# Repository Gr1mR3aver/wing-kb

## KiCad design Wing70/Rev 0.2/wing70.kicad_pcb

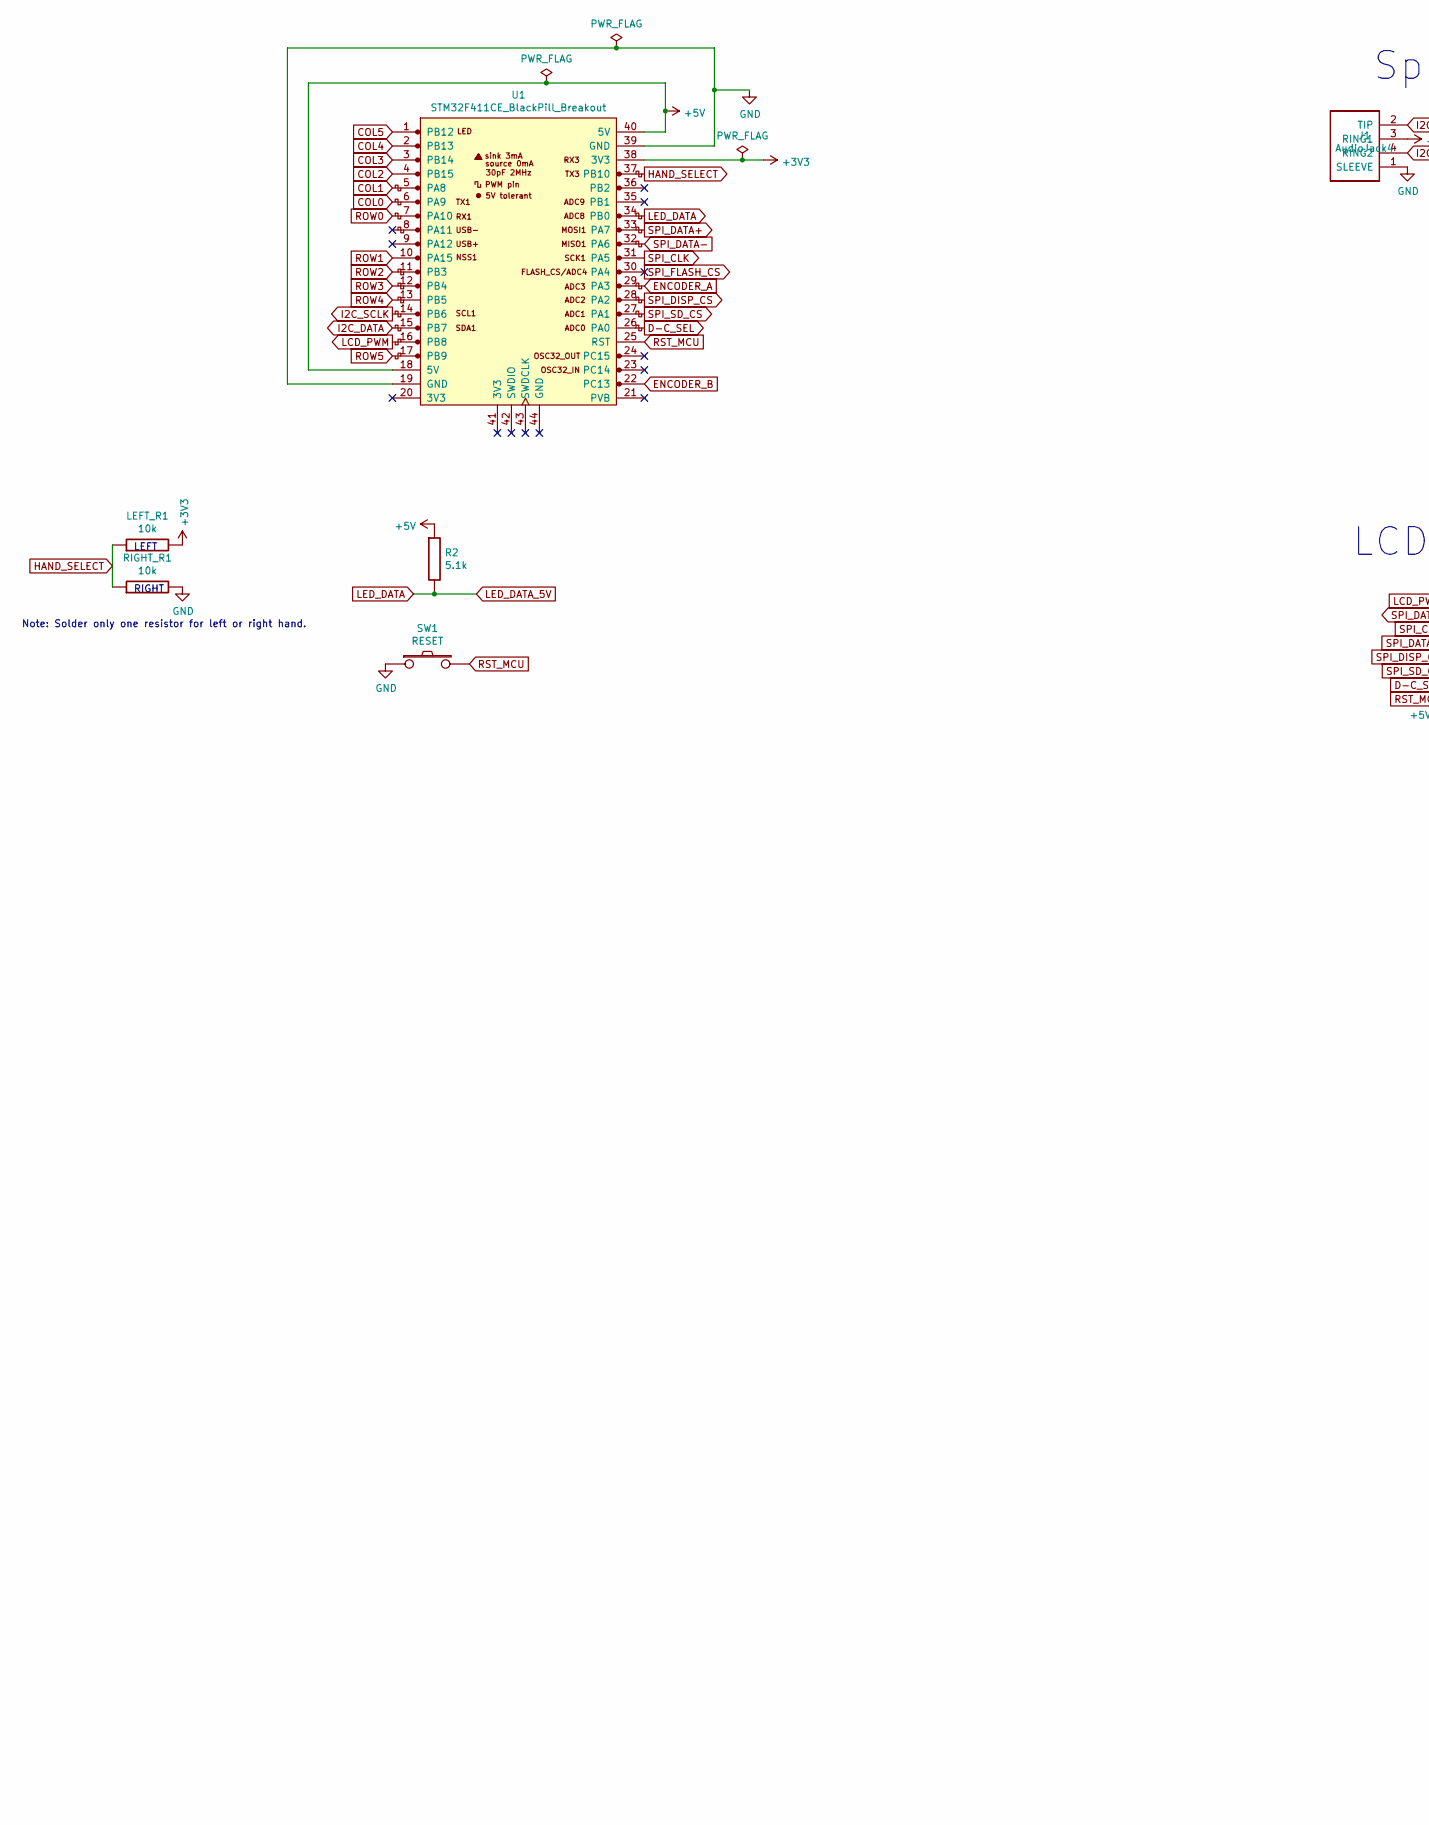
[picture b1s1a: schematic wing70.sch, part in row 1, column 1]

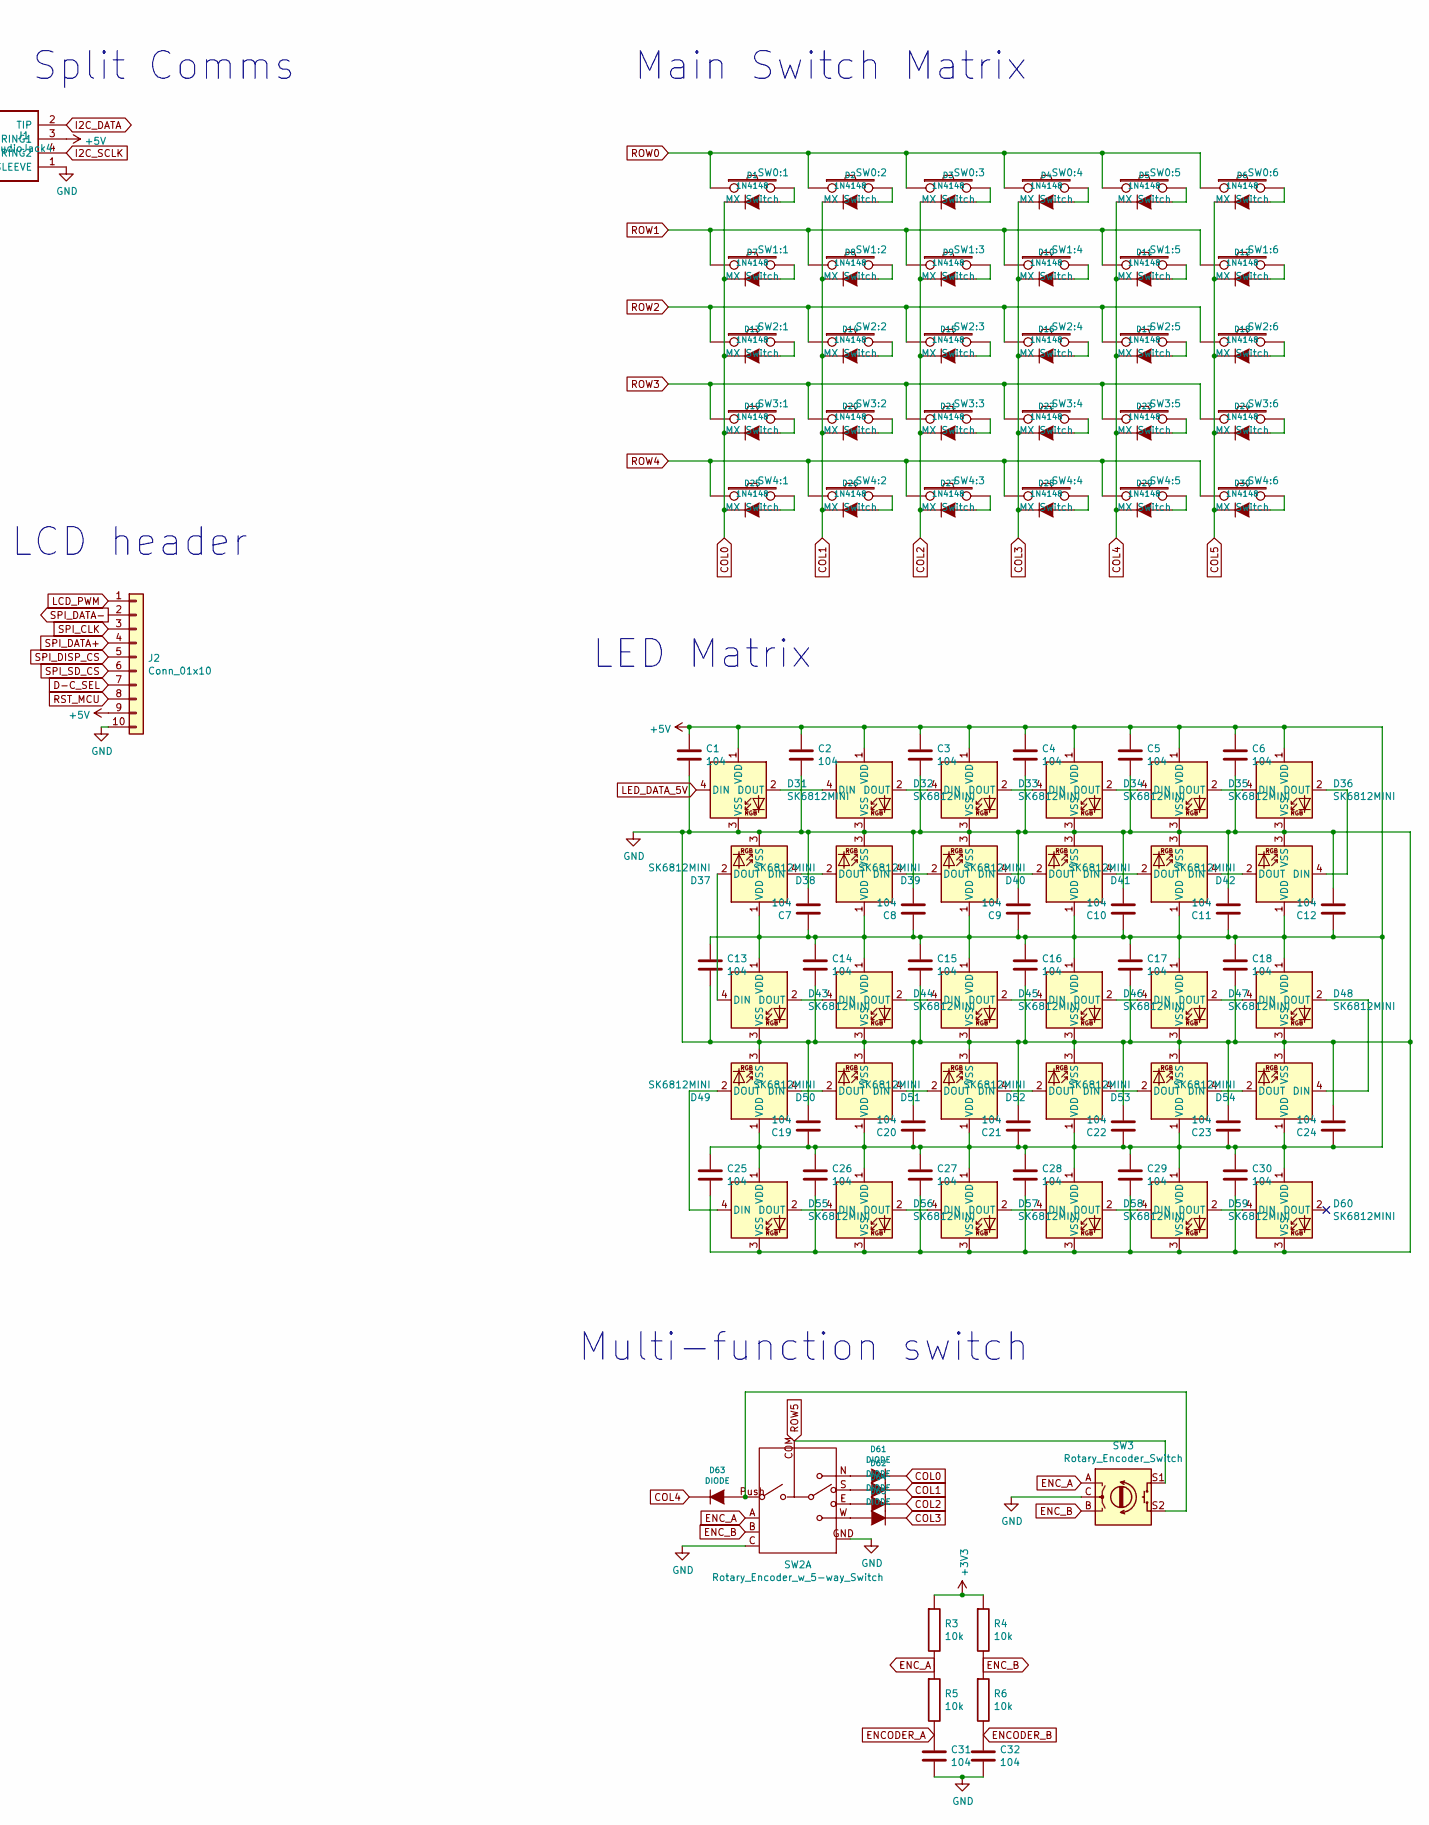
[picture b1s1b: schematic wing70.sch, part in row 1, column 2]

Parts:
C1, C2, C3, C4, C5, C6, C7, C8, C9, C10, C11, C12, C13, C14, C15, C16, C17, C18, C19, C20, C21, C22, C23, C24, C25, C26, C27, C28, C29, C30, C31, C32: 104; C_0805_2012Metric_Pad1.18x1.45mm_HandSolder
D1, D2, D3, D4, D5, D6, D7, D8, D9, D10, D11, D12, D13, D14, D15, D16, D17, D18, D19, D20, D21, D22, D23, D24, D25, D26, D27, D28, D29, D30: 1N4148; Add-on_diode_for_MX_socket
D31, D32, D33, D34, D35, D36, D37, D38, D39, D40, D41, D42, D43, D44, D45, D46, D47, D48, D49, D50, D51, D52, D53, D54, D55, D56, D57, D58, D59, D60: SK6812MINI; SK6812-MINI-E_reversible
D61, D62, D63, D64, D65: DIODE; Diode
J1: AudioJack4; TRRS_Jack_reversible_with_pads
J2: Conn_01x10; 1.8in_TFT_reversible-169x128_color-breakout
LEFT_R1: 10k; R_0805_2012Metric_Pad1.20x1.40mm_HandSolder
R2: 5.1k; R_0805_2012Metric_Pad1.20x1.40mm_HandSolder
R3, R4, R5, R6: 10k; R_0805_2012Metric_Pad1.20x1.40mm_HandSolder
RIGHT_R1: 10k; R_0805_2012Metric_Pad1.20x1.40mm_HandSolder
SW0:1, SW0:2, SW0:3, SW0:4, SW0:5, SW0:6, SW1:1, SW1:2, SW1:3, SW1:4, SW1:5, SW1:6, SW2:1, SW2:2, SW2:3, SW2:4, SW2:5, SW2:6, SW3:1, SW3:2, SW3:3, SW3:4, SW3:5, SW3:6, SW4:1, SW4:2, SW4:3, SW4:4, SW4:5, SW4:6: MX Switch; Kailh_socket_MX_optional_reversible
SW1: RESET; SW_Tactile_SPST_Angled_MJTP1117
SW2: Rotary_Encoder_w_5-way_Switch; RKJXT1F_reversible_EW_solder_jumpers
SW3: Rotary_Encoder_Switch; RotaryEncoder_Alps_EC11E-Switch_Vertical_H20mm
U1: STM32F411CE_BlackPill_Breakout; Blackpill_STM32F411CE

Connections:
+3V3: LEFT_R1.2, R3.1, R4.1, U1.38 (3V3)
+5V: C1.1, C2.1, C3.1, C4.1, C5.1, C6.1, C7.1, C8.1, C9.1, C10.1, C11.1, C12.1, C13.1, C14.1, C15.1, C16.1, C17.1, C18.1, C19.1, C20.1, C21.1, C22.1, C23.1, C24.1, C25.1, C26.1, C27.1, C28.1, C29.1, C30.1, D31.1 (VDD), D32.1 (VDD), D33.1 (VDD), D34.1 (VDD), D35.1 (VDD), D36.1 (VDD), D37.1 (VDD), D38.1 (VDD), D39.1 (VDD), D40.1 (VDD), D41.1 (VDD), D42.1 (VDD), D43.1 (VDD), D44.1 (VDD), D45.1 (VDD), D46.1 (VDD), D47.1 (VDD), D48.1 (VDD), D49.1 (VDD), D50.1 (VDD), D51.1 (VDD), D52.1 (VDD), D53.1 (VDD), D54.1 (VDD), D55.1 (VDD), D56.1 (VDD), D57.1 (VDD), D58.1 (VDD), D59.1 (VDD), D60.1 (VDD), J1.3 (RING1), J2.9, R2.1, U1.18 (5V), U1.40 (5V)
COL0: D1.2 (K), D7.2 (K), D13.2 (K), D19.2 (K), D25.2 (K), D61.2 (K), U1.6 (PA9)
COL1: D2.2 (K), D8.2 (K), D14.2 (K), D20.2 (K), D26.2 (K), D62.2 (K), U1.5 (PA8)
COL2: D3.2 (K), D9.2 (K), D15.2 (K), D21.2 (K), D27.2 (K), D64.2 (K), U1.4 (PB15)
COL3: D4.2 (K), D10.2 (K), D16.2 (K), D22.2 (K), D28.2 (K), D65.2 (K), U1.3 (PB14)
COL4: D5.2 (K), D11.2 (K), D17.2 (K), D23.2 (K), D29.2 (K), D63.2 (K), U1.2 (PB13)
COL5: D6.2 (K), D12.2 (K), D18.2 (K), D24.2 (K), D30.2 (K), U1.1 (PB12)
D-C_SEL: J2.7, U1.26 (PA0)
ENCODER_A: C31.1, R5.2, U1.29 (PA3)
ENCODER_B: C32.1, R6.2, U1.22 (PC13)
ENC_A: R3.2, R5.1, SW2.A, SW3.A
ENC_B: R4.2, R6.1, SW2.B, SW3.B
GND: C1.2, C2.2, C3.2, C4.2, C5.2, C6.2, C7.2, C8.2, C9.2, C10.2, C11.2, C12.2, C13.2, C14.2, C15.2, C16.2, C17.2, C18.2, C19.2, C20.2, C21.2, C22.2, C23.2, C24.2, C25.2, C26.2, C27.2, C28.2, C29.2, C30.2, C31.2, C32.2, D31.3 (VSS), D32.3 (VSS), D33.3 (VSS), D34.3 (VSS), D35.3 (VSS), D36.3 (VSS), D37.3 (VSS), D38.3 (VSS), D39.3 (VSS), D40.3 (VSS), D41.3 (VSS), D42.3 (VSS), D43.3 (VSS), D44.3 (VSS), D45.3 (VSS), D46.3 (VSS), D47.3 (VSS), D48.3 (VSS), D49.3 (VSS), D50.3 (VSS), D51.3 (VSS), D52.3 (VSS), D53.3 (VSS), D54.3 (VSS), D55.3 (VSS), D56.3 (VSS), D57.3 (VSS), D58.3 (VSS), D59.3 (VSS), D60.3 (VSS), J1.1 (SLEEVE), J2.10, RIGHT_R1.2, SW1.1, SW2.C, SW2.GND, SW3.C, U1.19 (GND), U1.39 (GND)
HAND_SELECT: LEFT_R1.1, RIGHT_R1.1, U1.37 (PB10)
I2C_DATA: J1.2 (TIP), U1.15 (PB7)
I2C_SCLK: J1.4 (RING2), U1.14 (PB6)
LCD_PWM: J2.1, U1.16 (PB8)
LED_DATA: D31.4 (DIN), R2.2, U1.34 (PB0)
unnamed: D1.1 (A), SW0:1.2
unnamed: D2.1 (A), SW0:2.2
unnamed: D3.1 (A), SW0:3.2
unnamed: D4.1 (A), SW0:4.2
unnamed: D5.1 (A), SW0:5.2
unnamed: D6.1 (A), SW0:6.2
unnamed: D7.1 (A), SW1:1.2
unnamed: D8.1 (A), SW1:2.2
unnamed: D9.1 (A), SW1:3.2
unnamed: D10.1 (A), SW1:4.2
unnamed: D11.1 (A), SW1:5.2
unnamed: D12.1 (A), SW1:6.2
unnamed: D13.1 (A), SW2:1.2
unnamed: D14.1 (A), SW2:2.2
unnamed: D15.1 (A), SW2:3.2
unnamed: D16.1 (A), SW2:4.2
unnamed: D17.1 (A), SW2:5.2
unnamed: D18.1 (A), SW2:6.2
unnamed: D19.1 (A), SW3:1.2
unnamed: D20.1 (A), SW3:2.2
unnamed: D21.1 (A), SW3:3.2
unnamed: D22.1 (A), SW3:4.2
unnamed: D23.1 (A), SW3:5.2
unnamed: D24.1 (A), SW3:6.2
unnamed: D25.1 (A), SW4:1.2
unnamed: D26.1 (A), SW4:2.2
unnamed: D27.1 (A), SW4:3.2
unnamed: D28.1 (A), SW4:4.2
unnamed: D29.1 (A), SW4:5.2
unnamed: D30.1 (A), SW4:6.2
unnamed: D31.2 (DOUT), D32.4 (DIN)
unnamed: D32.2 (DOUT), D33.4 (DIN)
unnamed: D33.2 (DOUT), D34.4 (DIN)
unnamed: D34.2 (DOUT), D35.4 (DIN)
unnamed: D35.2 (DOUT), D36.4 (DIN)
unnamed: D36.2 (DOUT), D42.4 (DIN)
unnamed: D37.2 (DOUT), D43.4 (DIN)
unnamed: D37.4 (DIN), D38.2 (DOUT)
unnamed: D38.4 (DIN), D39.2 (DOUT)
unnamed: D39.4 (DIN), D40.2 (DOUT)
unnamed: D40.4 (DIN), D41.2 (DOUT)
unnamed: D41.4 (DIN), D42.2 (DOUT)
unnamed: D43.2 (DOUT), D44.4 (DIN)
unnamed: D44.2 (DOUT), D45.4 (DIN)
unnamed: D45.2 (DOUT), D46.4 (DIN)
unnamed: D46.2 (DOUT), D47.4 (DIN)
unnamed: D47.2 (DOUT), D48.4 (DIN)
unnamed: D48.2 (DOUT), D54.4 (DIN)
unnamed: D49.2 (DOUT), D55.4 (DIN)
unnamed: D49.4 (DIN), D50.2 (DOUT)
unnamed: D50.4 (DIN), D51.2 (DOUT)
unnamed: D51.4 (DIN), D52.2 (DOUT)
unnamed: D52.4 (DIN), D53.2 (DOUT)
unnamed: D53.4 (DIN), D54.2 (DOUT)
unnamed: D55.2 (DOUT), D56.4 (DIN)
unnamed: D56.2 (DOUT), D57.4 (DIN)
unnamed: D57.2 (DOUT), D58.4 (DIN)
unnamed: D58.2 (DOUT), D59.4 (DIN)
unnamed: D59.2 (DOUT), D60.4 (DIN)
unnamed: D61.1 (A), SW2.N
unnamed: D62.1 (A), SW2.S
unnamed: D63.1 (A), SW2.Push, SW3.S2
unnamed: D64.1 (A), SW2.E
unnamed: D65.1 (A), SW2.W
ROW0: SW0:1.1, SW0:2.1, SW0:3.1, SW0:4.1, SW0:5.1, SW0:6.1, U1.7 (PA10)
ROW1: SW1:1.1, SW1:2.1, SW1:3.1, SW1:4.1, SW1:5.1, SW1:6.1, U1.10 (PA15)
ROW2: SW2:1.1, SW2:2.1, SW2:3.1, SW2:4.1, SW2:5.1, SW2:6.1, U1.11 (PB3)
ROW3: SW3:1.1, SW3:2.1, SW3:3.1, SW3:4.1, SW3:5.1, SW3:6.1, U1.12 (PB4)
ROW4: SW4:1.1, SW4:2.1, SW4:3.1, SW4:4.1, SW4:5.1, SW4:6.1, U1.13 (PB5)
ROW5: SW2.COM, SW3.S1, U1.17 (PB9)
RST_MCU: J2.8, SW1.2, U1.25 (RST)
SPI_CLK: J2.3, U1.31 (PA5)
SPI_DATA+: J2.4, U1.33 (PA7)
SPI_DATA-: J2.2, U1.32 (PA6)
SPI_DISP_CS: J2.5, U1.28 (PA2)
SPI_FLASH_CS: U1.30 (PA4)
SPI_SD_CS: J2.6, U1.27 (PA1)

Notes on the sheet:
Main Switch Matrix
Split Comms
Multi-function switch
LCD header
LED Matrix
Note: Solder only one resistor for left or right hand.
LEFT
RIGHT

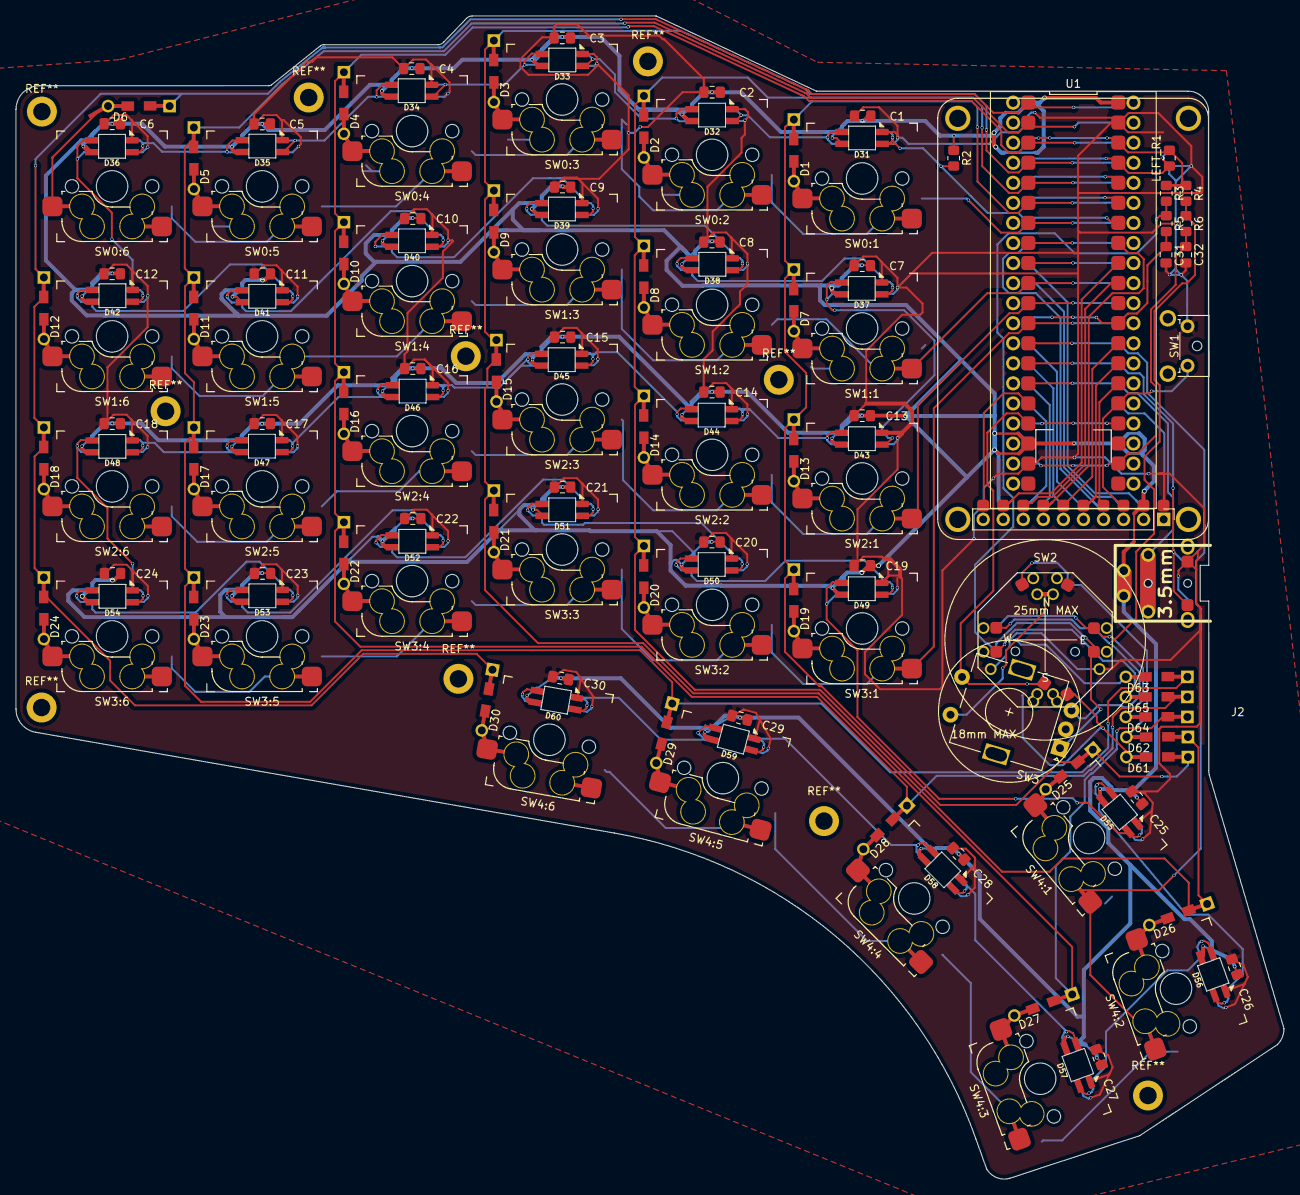
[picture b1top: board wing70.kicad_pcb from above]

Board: 2 copper layers, 160.5 x 147.2 mm, 140 parts (1 on the bottom side), 95 nets.

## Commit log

2021-02-10 Adding initial files
